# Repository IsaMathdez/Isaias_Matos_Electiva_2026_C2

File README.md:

# Isaias_Matos_Electiva_2026_C2
Curso Electiva: Diseño Mecatrónico, por el docente Carlos Pichardo.
Todas las tareas se encuentran el branch master.

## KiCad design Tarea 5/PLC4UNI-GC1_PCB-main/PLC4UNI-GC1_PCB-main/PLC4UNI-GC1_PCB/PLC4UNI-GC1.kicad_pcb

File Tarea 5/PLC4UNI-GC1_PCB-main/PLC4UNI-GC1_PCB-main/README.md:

# PLC4UNI-GC1_PCB
Proyecto PLC4UNI modelo GC1

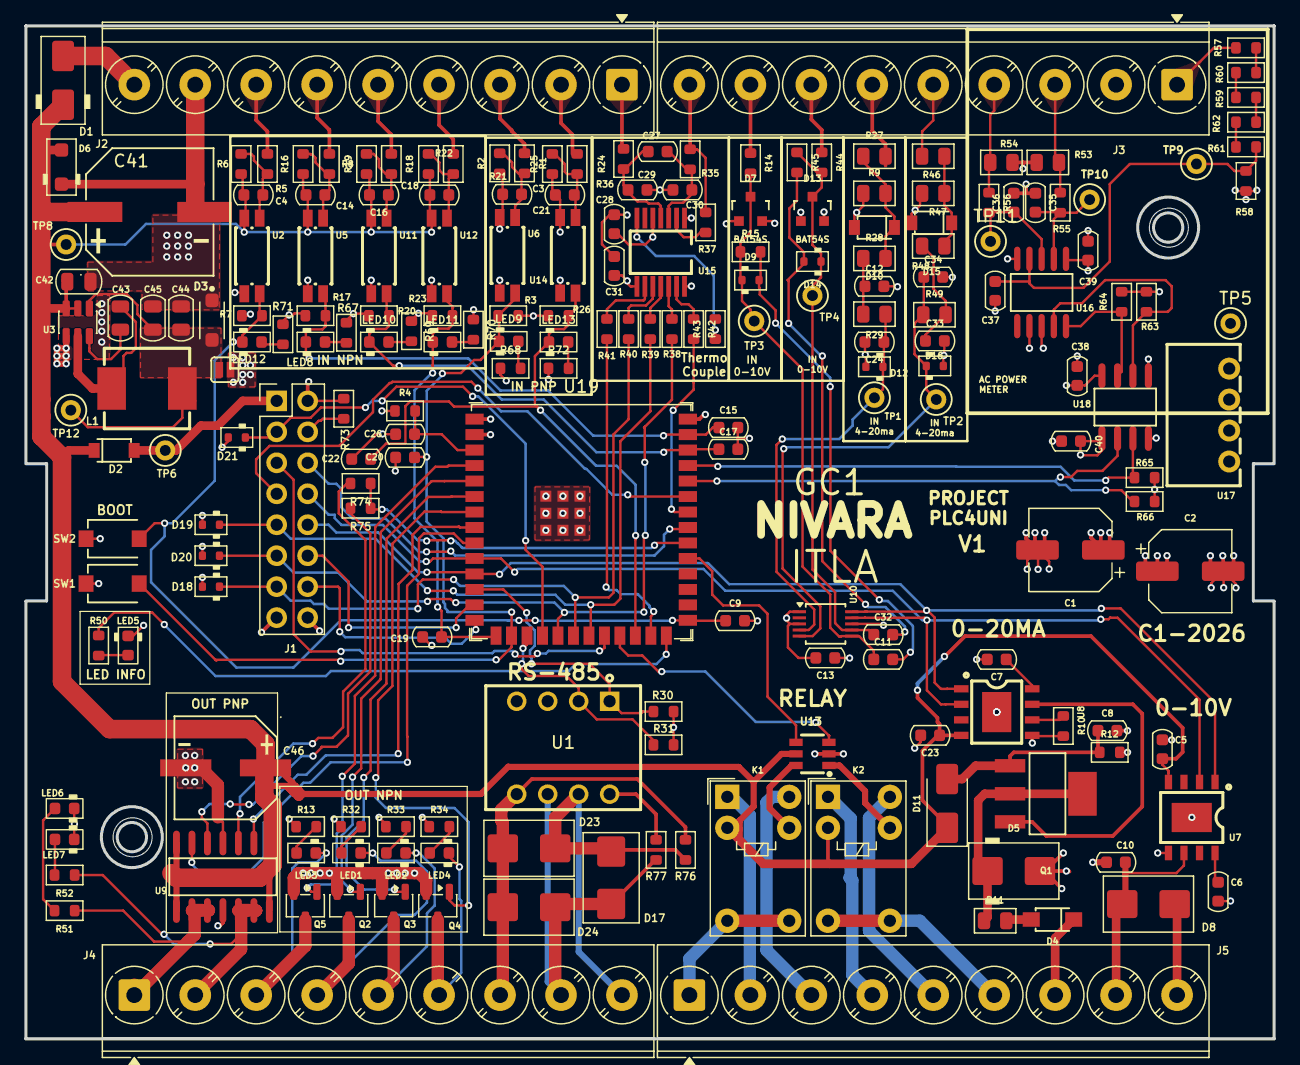
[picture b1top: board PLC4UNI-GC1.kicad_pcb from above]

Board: 4 copper layers, 102.4 x 83.1 mm, 205 parts (0 on the bottom side), 136 nets.

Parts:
C1, C2: 47UF; CP_Elec_6.3x7.7
C3, C4, C14, C16, C18, C21: 2.2NF; C_0603_1608Metric
C5, C6, C7, C23: C_0603; C_0603_1608Metric
C8, C26: 1uF; C_0603_1608Metric
C9, C15, C17, C19, C20, C22: 1NF; C_0603_1608Metric
C10: 100nF; C_0603_1608Metric
C11, C12, C13, C28, C31, C32, C33, C38, C39, C40: 100NF; C_0603_1608Metric
C24, C34: 47PF; C_0603_1608Metric
C27, C29, C30: 0.01UF; C_0603_1608Metric
C35, C36: 33NF; C_0603_1608Metric
C37: 68NF; C_0603_1608Metric
C41: 220uF; CAP-SMD_BD10.0-L10.3-W10.3-LS11.3-FD
C42: 10uF; C_0805_2012Metric
C43: 100NF; C_0805_2012Metric
C44, C45: 22uF; C_0805_2012Metric
C46: 100uF; CAP-SMD_BD8.0-L8.3-W8.3-FD
D1: MBRA340T; D_SMA
D2, D10, D15: 1N5819HW-7-F; SOD-123_L2.7-W1.6-LS3.7-RD
D3: SMF3.3; SMF3.3_SODFL3718X108N
D4: DSK120_C22466355; SOD-123FL_L2.7-W1.8-LS3.8-RD
D5: SMBJ28A; D_SMB
D6: SMF24CA; D_SOD-123F
D7, D13: BAT54S; SOT23-3_PO132
D8, D17: SMBJ12CA; D_SMB_TVS
D9, D12, D14, D16: PESD5Z3.3; D_SOD-523
D11: SMAJ12A; D_SMA
D18, D19, D20, D21: ESD5Z3.3T; D_SOD-523
D23, D24: SMBJ6.5CA; D_SMB_TVS
H1, H2: MountingHole; MountingHole_3.2mm_M3
J1: Conn_02x08_Odd_Even; PinHeader_2x08_P2.54mm_Vertical
J2, J3, J4, J5: Screw_Terminal_9_P5.00mm; TerminalBlock_Phoenix_PT-1,5-9-5.0-H_1x09_P5.00mm_Horizontal
JP1: Jumper_2_NO
K1, K2: G5V-1; Relay_SPDT_Omron_G5V-1
L1: APH0630T4R7M; IND-SMD_L7.0-W6.6_APH0630
LED1, LED2, LED3, LED4, LED5, LED6, LED7, LED8, LED9, LED10, LED11, LED12, LED13: LED_0603_Red; LED_0603_1608Metric
Q1: NCE60P04R; SOT-223-3_L6.5-W3.4-P2.30-LS7.0-BR
Q2, Q3, Q4, Q5: ZXMS6004FFQTA; SOT-23-3
R1, R5, R8, R18, R21, R24: 3.6K; R_0603_1608Metric
R2, R6, R16, R19, R22, R25: 3.3K; R_0603_1608Metric
R3, R7, R17, R20, R23, R26: 22K; R_0603_1608Metric
R4, R55, R56, R76, R77: 1K; R_0603_1608Metric
R9, R47: 120R; R_0805_2012Metric
R10, R13, R32, R33, R34, R51, R52, R67, R68, R69, R70, R71, R72: R_0603; R_0603_1608Metric
R11: 15R; R_0805_2012Metric
R12: 470K; R_0603_1608Metric
R14, R44, R50: 2.2K; R_0603_1608Metric
R15, R45: 1.05K; R_0603_1608Metric
R27, R46: 49.9R; R_0805_2012Metric
R28, R48: 47K; R_0805_2012Metric
R29, R49: 100K; R_0805_2012Metric
R30, R31: 10K; R_0603_1608Metric
R35, R36, R73, R74, R75: 0R; R_0603_1608Metric
R37: 20K; R_0603_1608Metric
R38, R39, R40, R41, R42, R43: 150; R_0603_1608Metric
R53, R54: 0.51; R_0805_2012Metric
R57, R59, R60, R61, R62: 390K; R_0603_1608Metric
R58: 510; R_0603_1608Metric
R63, R64, R65, R66: 4.7K; R_0603_1608Metric
SW1, SW2: TS-1088-AR02016; SW-SMD_L3.9-W3.0-P4.45
TP1, TP2, TP3, TP4, TP5, TP6, TP8, TP9, TP10, TP11, TP12: TestPoint_Hole1; TestPoint_WireHole
U1: TD301M485_C5451847; COMM-TH_TD301M485
U2, U5, U6, U11, U12, U14: AT3H4B-CUH-S; SSOP-4_L2.7-W4.6-P1.27-LS7.0-TL
U3: AP63203WU; TSOT-23-6
U7: GP8211S-TC50-EW; ESOP-8_L4.9-W3.9-P1.27-LS6.0-BL-EP
U8: GP8302-TC50-EW; ESOP-8_L4.9-W3.9-P1.27-LS6.0-BL-EP
U9: BTS723GWXUMA1; SOIC-14_L8.7-W3.9-P1.27-LS6.0-BL
U10: ADS1115IDGS; TSSOP-10_3x3mm_P0.5mm
U13: LK1802; SOT-23-6_L2.9-W1.6-P0.95-LS2.8-BR
U15: MAX31856MUD+; TSSOP-14_L5.0-W4.4-P0.65-LS6.4-BL
U16: BL0942; SSOP-10_L4.9-W3.9-P1.00-LS6.0-BL
U17: B0303S-1WR3_C7465185; PWRM-TH_BXXXXS-1WR3
U18: ISO7021DR; SOIC-8_L4.9-W3.9-P1.27-LS6.0-BL
U19: ESP32-S3-WROOM-1; ESP32-S3-WROOM-1U

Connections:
+3.3V: C1.1, C2.1, C13.1, C28.1, C31.1, C40.2, D7.2 (cathode), D13.2 (cathode), J1.2, JP1.2 (B), R3.2, R4.1, R7.2, R13.1, R17.2, R20.2, R23.2, R26.2, R30.1, R31.1, R32.1, R33.1, R34.1, R65.2, R66.2, R67.1, R68.1, R69.1, R70.1, R71.1, R72.1, R73.1, U1.4 (VCC), U9.11 (SPU), U10.8 (VDD), U15.5 (AVDD), U15.8 (DVDD), U17.2 (+Vin), U18.1 (VCC1), U19.2 (3V3)
+5V: D2.2 (A), J1.1, TP6.1 (1_1)
+24V: D1.2 (A), J2.9
/PowerSupply/ps_out: C44.1, C45.1, D3.A, JP1.1 (A), L1.2, TP12.1 (1_1), U3.1 (FB)
/PowerSupply/sw: C43.2, L1.1, U3.5 (SW)
/control/CON-IN-4-20MA_1: J3.6, R27.2
/control/CON-IN-4-20MA_2: J3.5, R46.2
/control/CON-IN_CT_N: J3.4, R54.2, R56.1
/control/CON-IN_CT_P: J3.3, R53.1, R55.1
/control/CON-IN_VAC_P: J3.1, R57.1
/control/CON_IN_0-10V_1: J3.8, R14.1
/control/CON_IN_0-10V_2: J3.7, R44.1
/control/CON_IN_NPN1: J2.7, R5.1
/control/CON_IN_NPN2: J2.6, R8.1
/control/CON_IN_NPN3: J2.5, R18.1
/control/CON_IN_NPN4: J2.4, R21.1
/control/CON_IN_PNP1: J2.3, R1.1
/control/CON_IN_PNP2: J2.2, R24.1
/control/CON_IN_TC+: J2.1, R36.1
/control/CON_IN_TC-: J3.9, R35.1, R37.1
/control/CON_OUT_0-10V: C10.1, D8.2 (A), J5.8, U7.6 (VOUT)
/control/CON_OUT_4-20MA: D4.1 (C), J5.7
/control/CON_OUT_NPN1: J4.3, LED3.1 (K), Q5.3 (D)
/control/CON_OUT_NPN2: J4.4, LED1.1 (K), Q2.3 (D)
/control/CON_OUT_NPN3: J4.5, LED2.1 (K), Q3.3 (D)
/control/CON_OUT_NPN4: J4.6, LED4.1 (K), Q4.3 (D)
/control/CON_OUT_PNP1: J4.1, R51.1, U9.9 (OUT2), U9.10 (OUT2)
/control/CON_OUT_PNP2: J4.2, R52.1, U9.12 (OUT1), U9.13 (OUT1)
/control/CON_OUT_RLY1_COM: J5.1, K1.5, K1.6
/control/CON_OUT_RLY1_NC: J5.2, K1.1
/control/CON_OUT_RLY1_NO: J5.3, K1.10
/control/CON_OUT_RLY2_COM: J5.6, K2.5, K2.6
/control/CON_OUT_RLY2_NC: J5.4, K2.1
/control/CON_OUT_RLY2_NO: J5.5, K2.10
/control/CON_RS485_A: D17.1 (K), D23.2 (A), J4.9, R76.1, U1.7 (B)
/control/CON_RS485_B: D17.2 (A), D24.2 (A), J4.8, R77.2, U1.6 (A)
/control/CON_RS485_G: D23.1 (K), D24.1 (K), J4.7, R76.2, U1.5 (RGND)
/control/EMRX: R66.1, U18.2 (OUTA), U19.36 (U0RXD/GPIO44/CLK_OUT2)
/control/EM_TX: R65.1, U18.3 (INB), U19.37 (U0TXD/GPIO43/CLK_OUT1)
/control/EN: C26.2, R4.2, U19.3 (EN)
/control/I2C_SCK: J1.10, U7.1 (SCLK), U8.1 (SLCK), U10.10 (SCL), U19.11 (GPIO18/U1RXD/ADC2_CH7/CLK_OUT3)
/control/I2C_SDA: J1.8, U7.2 (SDA), U8.2 (SDA), U10.9 (SDA), U19.10 (GPIO17/U1TXD/ADC2_CH6)
/control/IN-0-10V1/COM: C32.2, D14.2 (A), R45.2
/control/IN-0-10V1/OUT3V: C32.1, D13.3 (AK), D14.1 (K), R44.2, R45.1, TP4.1 (1_1), U10.7 (AIN3)
/control/IN-0-10V/COM: C11.2, D9.2 (A), R15.2
/control/IN-0-10V/OUT3V: C11.1, D7.3 (AK), D9.1 (K), R14.2, R15.1, TP3.1 (1_1), U10.6 (AIN2)
/control/IN-4-20MA1/OUT: C34.1, D16.1 (K), R49.1, TP2.1 (1_1), U10.5 (AIN1)
/control/IN-4-20MA/OUT: C24.1, D12.1 (K), R29.1, TP1.1 (1_1), U10.4 (AIN0)
/control/IN_NPN1: C9.1, LED12.1 (K), R7.1, SW1.2, U2.4, U19.27 (GPIO0/BOOT)
/control/IN_NPN2: C15.1, LED8.1 (K), R17.1, U5.4, U19.39 (GPIO1/TOUCH1/ADC1_CH0)
/control/IN_NPN3: C17.1, LED10.1 (K), R20.1, U11.4, U19.38 (GPIO2/TOUCH2/ADC1_CH1)
/control/IN_NPN4: C19.1, LED11.1 (K), R23.1, U12.4, U19.15 (GPIO3/TOUCH3/ADC1_CH2)
/control/IN_PNP1: C20.1, LED9.1 (K), R3.1, SW2.2, U6.4, U19.16 (GPIO46)
/control/IN_PNP2: C22.1, LED13.1 (K), R26.1, U14.4, U19.24 (GPIO47/SPICLK_P/SUBSPICLK_P_DIFF)
/control/LCD_CS: J1.7, U19.35 (MTMS/GPIO42)
/control/LCD_EN: J1.4, R73.2
/control/LED_INFO: R50.2, U19.26 (GPIO45)
/control/OUT-PNP/st1: R74.2, U9.3 (ST1)
/control/OUT-PNP/st2: R75.2, U9.5 (ST2)
/control/OUT_NPN1: Q5.1 (IN), U19.4 (GPIO4/TOUCH4/ADC1_CH3)
/control/OUT_NPN2: Q2.1 (IN), U19.5 (GPIO5/TOUCH5/ADC1_CH4)
/control/OUT_NPN3: Q3.1 (IN), U19.6 (GPIO6/TOUCH6/ADC1_CH5)
/control/OUT_NPN4: Q4.1 (IN), U19.7 (GPIO7/TOUCH7/ADC1_CH6)
/control/OUT_PNP1: U9.2 (IN1), U19.8 (GPIO15/U0RTS/ADC2_CH4/XTAL_32K_P)
/control/OUT_PNP2: U9.6 (IN2), U19.9 (GPIO16/U0CTS/ADC2_CH5/XTAL_32K_N)
/control/OUT_RLY1: U13.3 (1B), U19.23 (GPIO21)
/control/OUT_RLY2: U13.4 (2B), U19.31 (GPIO38/FSPIWP/SUBSPIWP)
/control/RESET: J1.5, U19.22 (GPIO14/TOUCH14/ADC2_CH3/FSPIWP/FSPIDQS/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)
/control/RS485-RX: R30.2, U1.1 (RXD), U19.12 (GPIO8/TOUCH8/ADC1_CH7/SUBSPICS1)
/control/RS485-TX: R31.2, U1.2 (TXD), U19.17 (GPIO9/TOUCH9/ADC1_CH8/FSPIHD/SUBSPIHD)
/control/SD_CS: D21.1 (K), J1.3, U19.18 (GPIO10/TOUCH10/ADC1_CH9/FSPICS0/FSPIIO4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)
/control/SPI_CLK: D18.1 (K), J1.13, R40.2, U19.20 (GPIO12/TOUCH12/ADC2_CH1/FSPICLK/FSPIIO6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)
/control/SPI_MISO: D19.1 (K), J1.9, R39.2, U19.21 (GPIO13/TOUCH13/ADC2_CH2/FSPIQ/FSPIIO7/S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)
/control/SPI_MOSI: D20.1 (K), J1.11, R38.2, U19.19 (GPIO11/TOUCH11/ADC2_CH0/FSPID/FSPIIO5/S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)
/control/ST1_ST2: R74.1, R75.1, U19.32 (MTCK/GPIO39/CLK_OUT3/SUBSPICS1)
/control/TC_FAULT: R42.2, U19.34 (MTDI/GPIO41/CLK_OUT1)
/control/TEMP_CS: R41.2, U19.25 (GPIO48/SPICLK_N/SUBSPICLK_N_DIFF)
/control/TP_INT: J1.6, U19.33 (MTDO/GPIO40/CLK_OUT2)
/control/USB+: J1.14, U19.14 (GPIO20/U1CTS/ADC2_CH9/CLK_OUT1/USB_D+)
/control/USB-: J1.12, U19.13 (GPIO19/U1RTS/ADC2_CH8/CLK_OUT2/USB_D-)
Earth: C35.1, C36.2, C37.1, C38.1, C39.1, J3.2, R53.2, R54.1, R58.1, U16.5 (GND), U16.7 (SEL), U17.3 (-Vout), U18.5 (GND2)
GND: C1.2, C2.2, C3.2, C5.2, C6.2, C7.2, C8.2, C9.2, C10.2, C12.2, C13.2, C15.2, C17.2, C19.2, C20.2, C21.2, C22.2, C23.2, C24.2, C26.1, C28.2, C29.2, C30.2, C31.2, C33.2, C34.2, C40.1, C41.2, C42.2, C44.2, C45.2, C46.2, D3.C, D5.2 (A), D6.1 (K), D7.1 (Anode), D8.1 (K), D10.2 (A), D12.2 (A), D13.1 (Anode), D15.2 (A), D16.2 (A), D18.2 (A), D19.2 (A), D20.2 (A), D21.2 (A), J1.15, J1.16, J2.8, J5.9, LED5.1 (K), LED6.1 (K), LED7.1 (K), Q2.2 (OUT), Q3.2 (OUT), Q4.2 (OUT), Q5.2 (OUT), R2.1, R9.1, R10.2, R12.2, R25.1, R47.1, SW1.1, SW2.1, U1.3 (GND), U2.3, U3.4 (GND), U5.3, U6.2, U6.3, U7.5 (GND), U7.9 (EP), U8.5 (GND), U8.9 (EP), U9.4 (GND), U10.1 (ADDR), U10.3 (GND), U11.3, U12.3, U13.2 (E), U14.2, U14.3, U15.1 (AGND), U15.14 (DGND), U17.1 (-Vin), U18.4 (GND1), U19.1 (GND), U19.40 (GND), U19.41 (GND)
unnamed: C3.1, R1.2, R2.2, U6.1
unnamed: C4.1, R5.2, R6.2, U2.1
unnamed: C12.1, R28.1, R29.2
unnamed: C14.1, R8.2, R16.2, U5.1
unnamed: C16.1, R18.2, R19.2, U11.1
unnamed: C18.1, R21.2, R22.2, U12.1
unnamed: C21.1, R24.2, R25.2, U14.1
unnamed: C33.1, R48.1, R49.2
unnamed: D4.2 (A), R11.2
unnamed: D5.1 (K), Q1.2, Q1.4, R11.1
unnamed: D10.1 (K), R9.2, R27.1, R28.2
unnamed: C8.1, D11.2 (A2), Q1.1, R12.1
unnamed: D15.1 (K), R46.1, R47.2, R48.2
unnamed: LED1.2 (A), R32.2
unnamed: LED2.2 (A), R33.2
unnamed: LED3.2 (A), R13.2
unnamed: LED4.2 (A), R34.2
unnamed: LED5.2 (A), R50.1
unnamed: LED6.2 (A), R51.2
unnamed: LED7.2 (A), R52.2
unnamed: LED8.2 (A), R67.2
unnamed: LED9.2 (A), R68.2
unnamed: LED10.2 (A), R69.2
unnamed: LED11.2 (A), R70.2
unnamed: LED12.2 (A), R71.2
unnamed: LED13.2 (A), R72.2
unnamed: R57.2, R59.1
unnamed: R59.2, R60.1
unnamed: R60.2, R61.1
unnamed: R61.2, R62.1
unnamed: R77.1, U1.8 (VO)
unnamed: C43.1, U3.6 (BST)
unnamed: C6.1, U7.8 (V5V)
unnamed: Q1.3, U8.7 (IOUT)
unnamed: R10.1, U8.6 (SET)
unnamed: C7.1, U8.8 (V5V)
unnamed: K2.9, U13.1 (1C)
unnamed: K1.9, U13.6 (2C)
unnamed: R37.2, U15.2 (BIAS)
unnamed: R40.1, U15.10 (SCK)
unnamed: R38.1, U15.12 (SDI)
unnamed: R39.1, U15.11 (SDO)
unnamed: C27.2, C29.1, R36.2, U15.4 (T+)
unnamed: C27.1, C30.1, R35.2, U15.3 (T-)
unnamed: R41.1, U15.9 (~CS)
unnamed: R43.1, U15.7 (~DRDY)
unnamed: R42.1, U15.13 (~FAULT)
unnamed: C36.1, R56.2, TP11.1 (1_1), U16.3 (IN)
unnamed: C35.2, R55.2, TP10.1 (1_1), U16.2 (IP)
unnamed: R63.1, U16.9 (RX/SDI), U18.6 (OUTB)
unnamed: R64.1, U16.10 (TX/SDO), U18.7 (INA)
unnamed: C37.2, R58.2, R62.2, TP9.1 (1_1), U16.4 (VP)
VCC: C38.2, C39.2, R63.2, R64.2, TP5.1 (1_1), U16.1 (VDD), U16.8 (SCLK_BPS), U17.4 (+Vout), U18.8 (VCC2)
VDC: C4.2, C5.1, C14.2, C16.2, C18.2, C23.1, C41.1, C42.1, C46.1, D1.1 (K), D2.1 (K), D6.2 (A), D11.1 (A1), K1.2, K2.2, R6.1, R16.1, R19.1, R22.1, TP8.1 (1_1), U2.2, U3.2 (EN), U3.3 (IN), U5.2, U7.4 (VCC), U8.4 (VCC), U9.1 (VBB), U9.7 (VBB), U9.8 (VBB), U9.14 (VBB), U11.2, U12.2, U13.5 (COM)

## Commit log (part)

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2026-05-18 Primero
2026-05-18 Segundo
2026-05-18 Tercero
2026-05-18 Primero alt
2026-05-18 Cuarto
2026-05-20 quinto: Añadido Tarea 1 carpeta
2026-05-20 Sexto
2026-05-20 Septimo
2026-05-20 Octavo
2026-05-20 Segundo alt
2026-05-20 Tarea 1 completada
2026-05-20 New read me
2026-06-11 Tarea 2 completada
